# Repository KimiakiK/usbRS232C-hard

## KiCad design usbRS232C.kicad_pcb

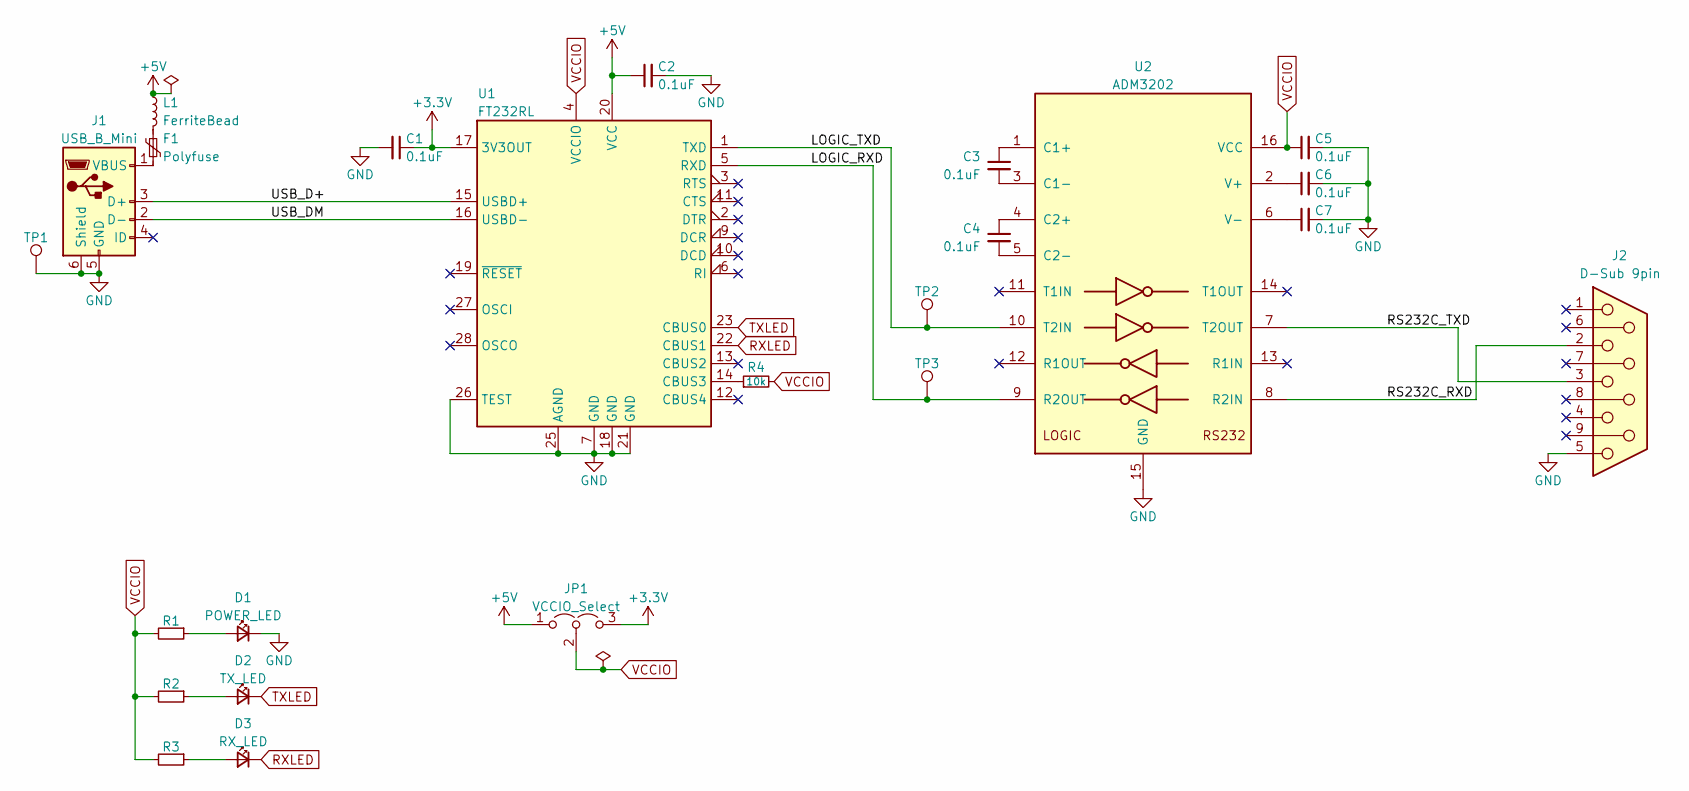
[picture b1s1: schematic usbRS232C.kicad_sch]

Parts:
C1, C2, C3, C4, C5, C6, C7: 0.1uF; 1608Metric
D1: POWER_LED; 1608Metric
D2: TX_LED; 1608Metric
D3: RX_LED; 1608Metric
F1: Polyfuse; 1608Metric
J1: USB_B_Mini; Mini USB UX60SC-MB-5ST
J2: D-Sub 9pin; DSUB-9_Male_Horizontal_P2.77x2.84mm_EdgePinOffset7.70mm_Hou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
JP1: VCCIO_Select; Jumper_3P
L1: FerriteBead; 1608Metric
R1, R2, R3: R; 1608Metric
R4: 10k; 1608Metric
TP1, TP2, TP3: TestPoint; TestPoint_THTPad_2.0x2.0mm_Drill1.0mm
U1: FT232RL; SSOP-28_5.3x10.2mm_P0.65mm
U2: ADM3202; SOIC-16_3.9x9.9mm_P1.27mm

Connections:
+3.3V: C1.1, JP1.3 (B), U1.17 (3V3OUT)
+5V: C2.1, JP1.1 (A), L1.1, U1.20 (VCC)
/LOGIC_RXD: TP3.1, U1.5 (RXD), U2.9 (R2OUT)
/LOGIC_TXD: TP2.1, U1.1 (TXD), U2.10 (T2IN)
/RS232C_RXD: J2.2, U2.8 (R2IN)
/RS232C_TXD: J2.3, U2.7 (T2OUT)
/USB_D+: J1.3 (D+), U1.15 (USBD+)
/USB_DM: J1.2 (D-), U1.16 (USBD-)
GND: C1.2, C2.2, C5.2, C6.2, C7.2, D1.1 (K), J1.5 (GND), J1.6 (Shield), J2.5, TP1.1, U1.7 (GND), U1.18 (GND), U1.21 (GND), U1.25 (AGND), U1.26 (TEST), U2.15 (GND)
unnamed: D1.2 (A), R1.1
unnamed: D2.2 (A), R2.1
unnamed: D3.2 (A), R3.1
unnamed: F1.1, L1.2
unnamed: F1.2, J1.1 (VBUS)
unnamed: R4.1, U1.14 (CBUS3)
unnamed: C3.1, U2.1 (C1+)
unnamed: C3.2, U2.3 (C1-)
unnamed: C4.1, U2.4 (C2+)
unnamed: C4.2, U2.5 (C2-)
unnamed: C6.1, U2.2 (V+)
unnamed: C7.1, U2.6 (V-)
RXLED: D3.1 (K), U1.22 (CBUS1)
TXLED: D2.1 (K), U1.23 (CBUS0)
VCCIO: C5.1, JP1.2 (C), R1.2, R2.2, R3.2, R4.2, U1.4 (VCCIO), U2.16 (VCC)

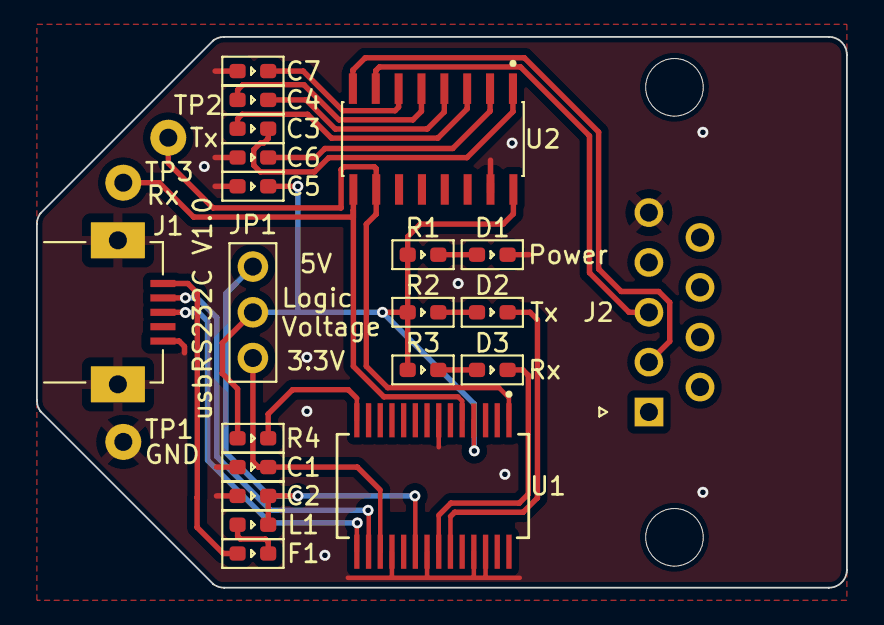
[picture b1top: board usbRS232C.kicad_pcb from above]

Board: 2 copper layers, 45.0 x 30.6 mm, 24 parts (0 on the bottom side), 24 nets.

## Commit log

2023-03-20 基板V1.0
